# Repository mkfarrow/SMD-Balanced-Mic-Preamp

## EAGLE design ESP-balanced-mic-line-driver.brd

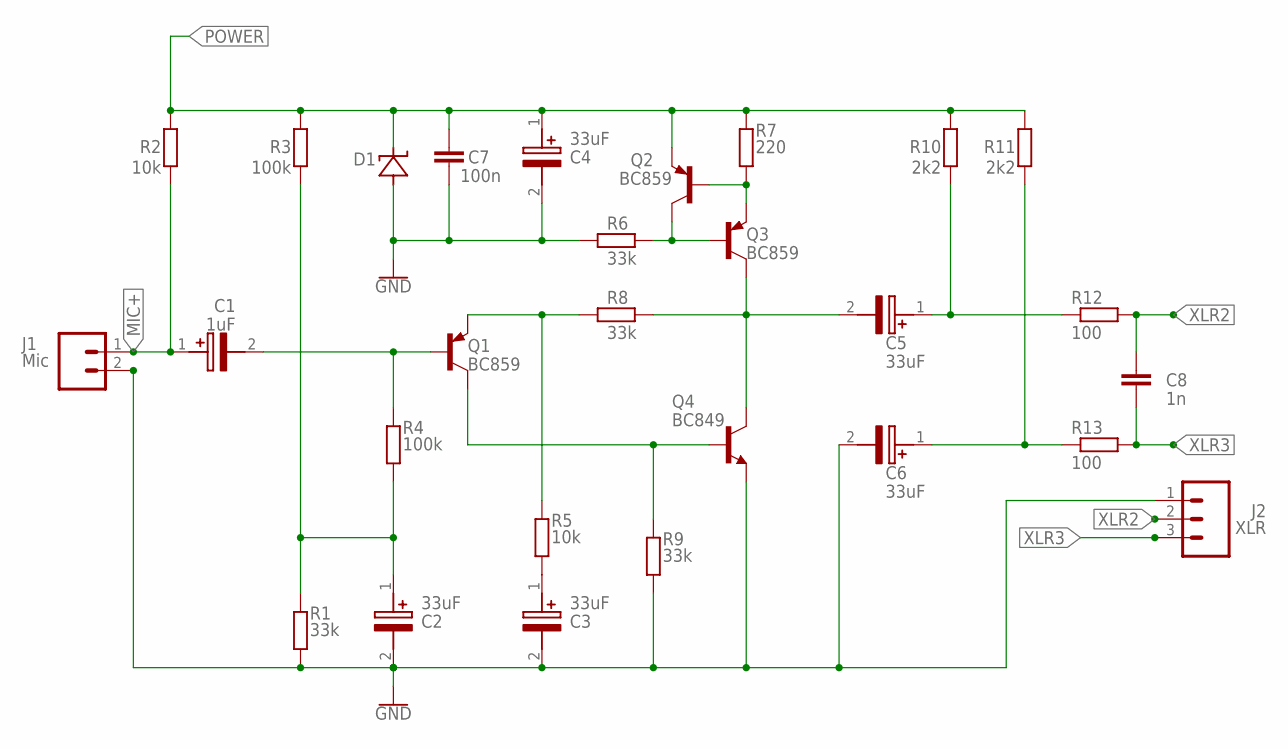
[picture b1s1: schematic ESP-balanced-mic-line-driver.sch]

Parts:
C1: 1uF; CAPAE530X550N
C2, C3, C4, C5, C6: 33uF; CAPAE530X550N
C7: 100n; C1210
C8: 1n; C0805
D1: ZENER_D; SOD123
J1: Mic; 1X02
J2: XLR; 1X03
Q1, Q2, Q3: BC859; SOT23-BEC
Q4: BC849; SOT23-BEC
R1, R6, R8, R9: 33k; R0603
R2, R5: 10k; R0603
R3, R4: 100k; R0603
R7: 220; R0603
R10, R11: 2k2; R0603
R12, R13: 100; R0603

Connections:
GND: C2.2 (-), C3.2 (-), C4.2 (-), C6.2 (-), C7.2, D1.A, J1.2, J2.1, Q4.E, R1.1, R6.1, R9.1
MIC+: C1.1 (+), J1.1, R2.1
unnamed: C5.2 (-), Q3.C, Q4.C, R8.2
unnamed: Q2.C, Q3.B, R6.2
unnamed: C3.1 (+), R5.1
unnamed: C5.1 (+), R10.1, R12.1
unnamed: C6.1 (+), R11.1, R13.1
unnamed: Q2.B, Q3.E, R7.1
unnamed: C2.1 (+), R1.2, R3.1, R4.1
unnamed: C1.2 (-), Q1.B, R4.2
unnamed: Q1.E, R5.2, R8.1
unnamed: Q1.C, Q4.B, R9.2
POWER: C4.1 (+), C7.1, D1.C, Q2.E, R2.2, R3.2, R7.2, R10.2, R11.2
XLR2: C8.1, J2.2, R12.2
XLR3: C8.2, J2.3, R13.2

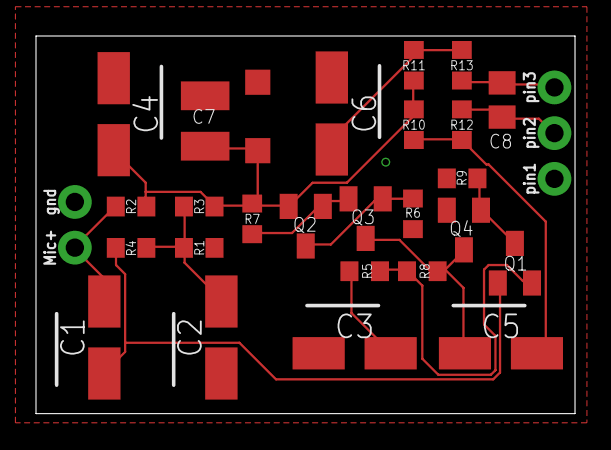
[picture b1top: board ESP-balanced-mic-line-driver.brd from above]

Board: 2 copper layers, 29.9 x 21.0 mm, 28 parts (0 on the bottom side), 15 nets.

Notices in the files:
parts and their libraries:
SparkFun-PowerSymbols: Licensing: Creative Commons ShareAlike 4.0 International - https://creativecommons.org/licenses/by-sa/4.0
